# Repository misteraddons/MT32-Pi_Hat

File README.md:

# MT32-Pi_Hat

A simple hat to connect a MiSTer FPGA IO board to a Raspberry Pi 3A 
Intended for use with the ao486 core and MT32-Pi project
 
Required accessories:
- 128x64 I2C OLED (https://www.amazon.com/IZOKEE-Display-SSD1306-Raspberry-White-IIC/dp/B076PDVFQD)
- Male to Male USB 3.0 cable
- Standard 2x20 pin header (not taller pin header like what MiSTer uses)
- USB 3.0 port (https://lcsc.com/product-detail/USB-Connectors_Jing-Extension-of-the-Electronic-Co-LCSC-A-F-90degree-3-0Outside-the-buckle-copper-shell-curling-has-curled-Not-high-temperature_C69073.html)
- M2.5 mounting hardware

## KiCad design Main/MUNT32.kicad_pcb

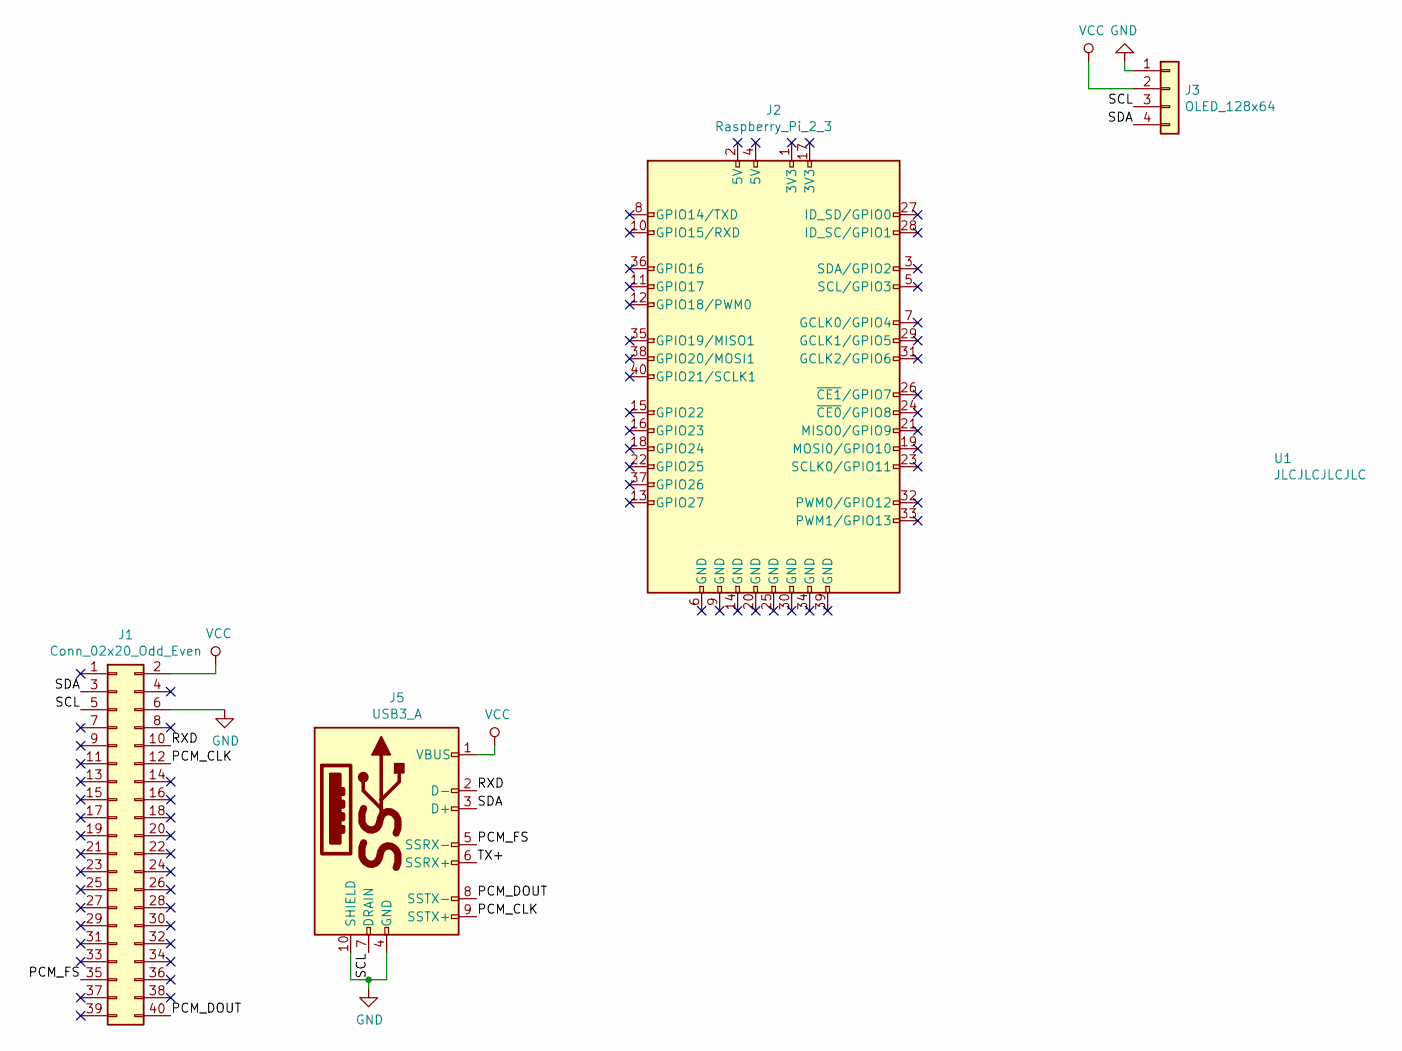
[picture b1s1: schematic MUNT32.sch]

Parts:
J1: Conn_02x20_Odd_Even; PinSocket_2x20_P2.54mm_Vertical
J2: Raspberry_Pi_2_3; Raspberry Pi 3A+
J3: OLED_128x64
J5: USB3_A
U1: JLCJLCJLCJLC

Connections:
/PCM_CLK: J1.12, J5.9 (SSTX+)
/PCM_DOUT: J1.40, J5.8 (SSTX-)
/PCM_FS: J1.35, J5.5 (SSRX-)
/RXD: J1.10, J5.2 (D-)
/SCL: J1.5, J3.3, J5.7 (DRAIN)
/SDA: J1.3, J3.4, J5.3 (D+)
/TX+: J5.6 (SSRX+)
GND: J1.6, J3.1, J5.4 (GND), J5.10 (SHIELD)
VCC: J1.2, J3.2, J5.1 (VBUS)

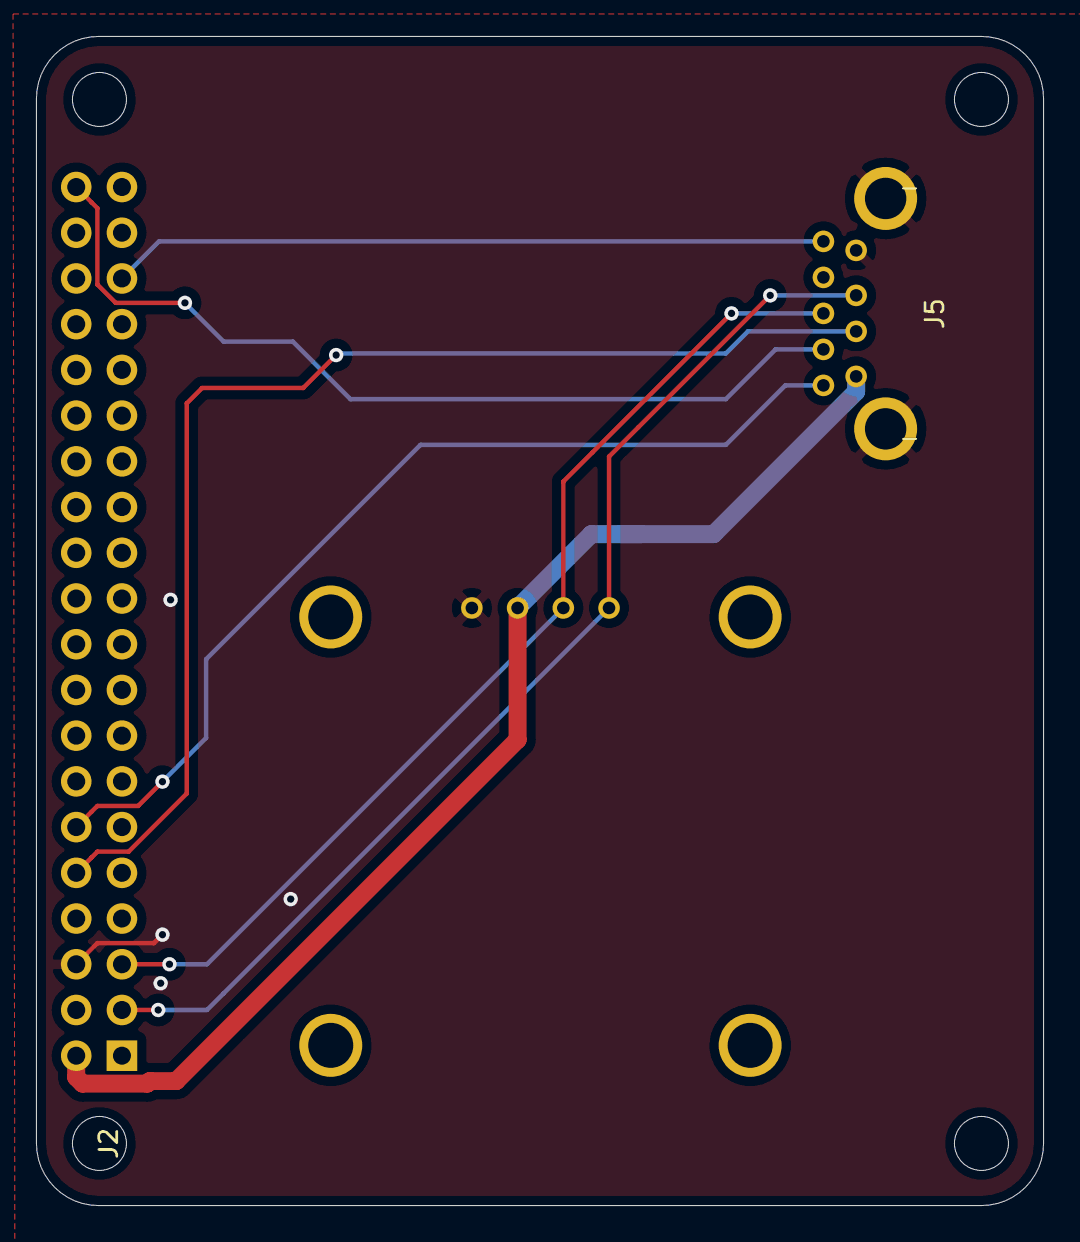
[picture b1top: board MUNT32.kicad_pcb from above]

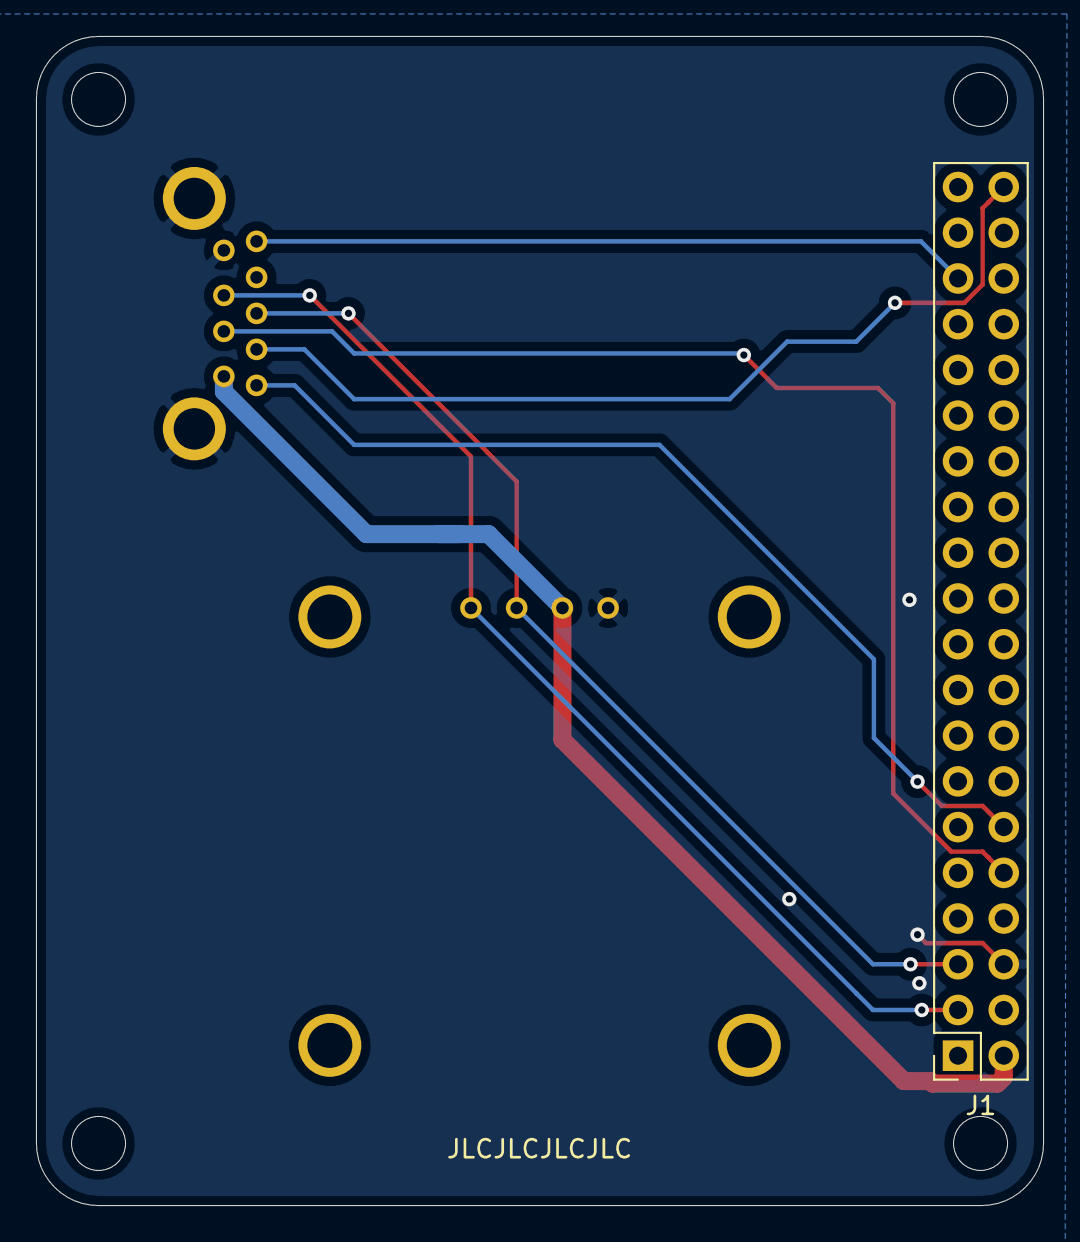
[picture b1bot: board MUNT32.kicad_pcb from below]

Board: 2 copper layers, 55.9 x 64.9 mm, 5 parts (2 on the bottom side), 8 nets.
